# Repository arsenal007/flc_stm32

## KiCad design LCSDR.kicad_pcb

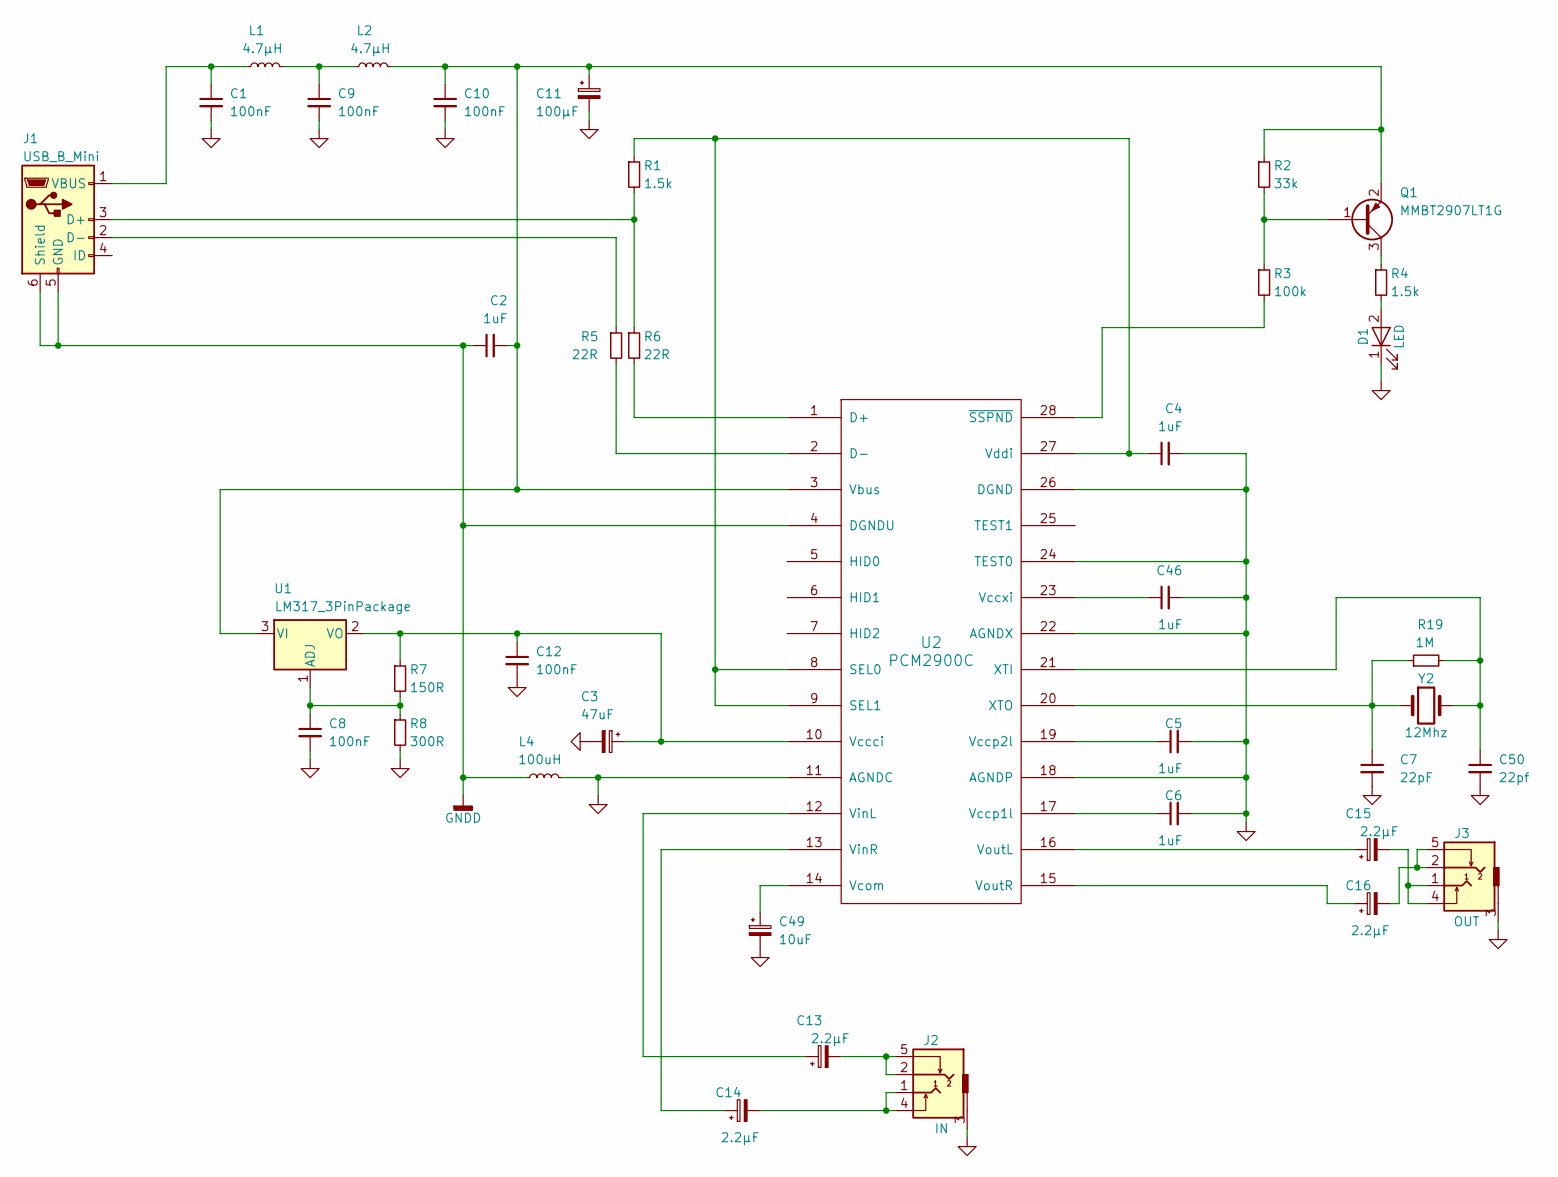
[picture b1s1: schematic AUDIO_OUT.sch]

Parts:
C1, C8, C9, C10, C12: 100nF; C_1206_0603
C2, C4, C5, C6, C46: 1uF; C_1206_0603
C3: 47uF; CP_Tantalum_Case-D_EIA-7343-31_Wave
C7: 22pF; C_1206_0603
C11: 100µF; CP_Tantalum_Case-D_EIA-7343-31_Wave
C13, C14, C15, C16: 2.2µF; CP_Tantalum_Case-A_EIA-3216-18_Wave
C49: 10uF; CP_Tantalum_Case-A_EIA-3216-18_Wave
C50: 22pf; C_1206_0603
D1: LED; LED_0603_HandSoldering
J1: USB_B_Mini; USB_Mini-B
J2: IN; audio_jack_3_5mm_PJ307
J3: OUT; audio_jack_3_5mm_PJ307
L1, L2: 4.7µH; Choke_CD54
L4: 100uH; Choke_Horizontal_RM10mm
Q1: MMBT2907LT1G; SOT-23
R1, R4: 1.5k; R_1206_0603
R2: 33k; R_1206_0603
R3: 100k; R_1206_0603
R5, R6: 22R; R_1206_0603
R7: 150R; R_1206_0603
R8: 300R; R_1206_0603
R19: 1M; R_1206_0603
U1: LM317_3PinPackage; SOT-223-3_TabPin2
U2: PCM2900C; SSOP-28_5.3x10.2mm_Pitch0.65mm
Y2: 12Mhz; Crystal_HC49-U_Vertical

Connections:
GND: C1.2, C3.2, C4.2, C5.2, C6.2, C7.2, C8.2, C9.2, C10.2, C11.2, C12.2, C46.2, C49.2, C50.2, D1.1 (K), J2.3, J3.3, L4.2, R8.2, U2.11 (AGNDC), U2.18 (AGNDP), U2.22 (AGNDX), U2.24 (TEST0), U2.26 (DGND)
GNDD: C2.1, J1.5 (GND), J1.6 (Shield), L4.1, U2.4 (DGNDU)
unnamed: C1.1, J1.1 (VBUS), L1.1
unnamed: C4.1, R1.1, U2.8 (SEL0), U2.9 (SEL1), U2.27 (Vddi)
unnamed: C5.1, U2.19 (Vccp2l)
unnamed: C6.1, U2.17 (Vccp1l)
unnamed: C7.1, R19.1, U2.20 (XTO), Y2.1
unnamed: C8.1, R7.2, R8.1, U1.1 (ADJ)
unnamed: C9.1, L1.2, L2.1
unnamed: C2.2, C10.1, C11.1, L2.2, Q1.2 (E), R2.1, U1.3 (VI), U2.3 (Vbus)
unnamed: C3.1, C12.1, R7.1, U1.2 (VO), U2.10 (Vccci)
unnamed: C13.1, U2.12 (VinL)
unnamed: C13.2, J2.2, J2.5
unnamed: C14.1, U2.13 (VinR)
unnamed: C14.2, J2.1, J2.4
unnamed: C15.1, U2.16 (VoutL)
unnamed: C15.2, J3.1, J3.4
unnamed: C16.1, U2.15 (VoutR)
unnamed: C16.2, J3.2, J3.5
unnamed: C46.1, U2.23 (Vccxi)
unnamed: C49.1, U2.14 (Vcom)
unnamed: C50.1, R19.2, U2.21 (XTI), Y2.2
unnamed: D1.2 (A), R4.2
unnamed: J1.2 (D-), R5.1
unnamed: J1.3 (D+), R1.2, R6.1
unnamed: Q1.1 (B), R2.2, R3.1
unnamed: Q1.3 (C), R4.1
unnamed: R3.2, U2.28 (~SSPND)
unnamed: R5.2, U2.2 (D-)
unnamed: R6.2, U2.1 (D+)

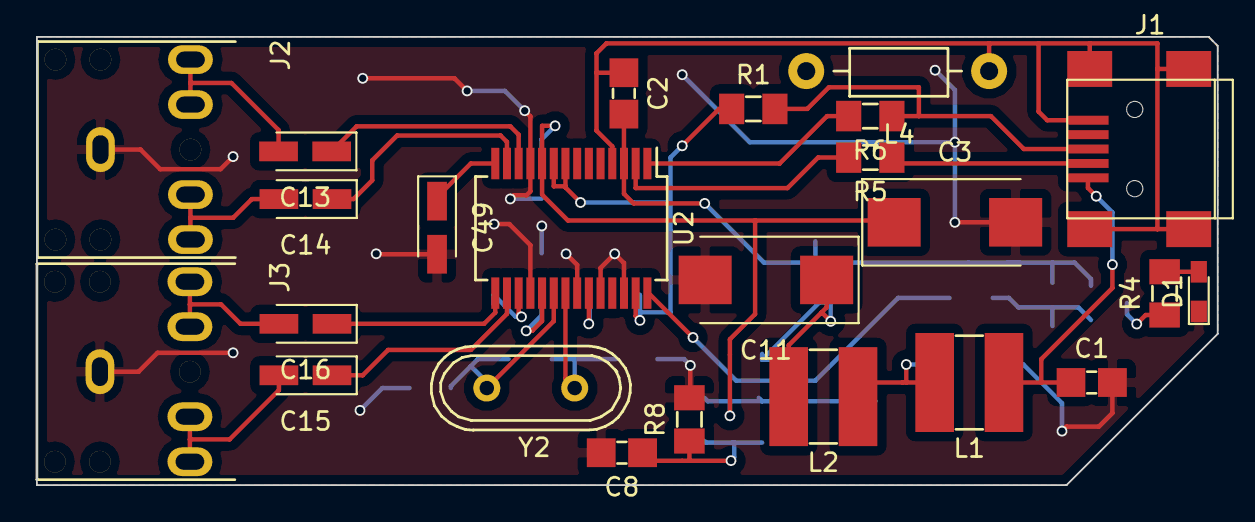
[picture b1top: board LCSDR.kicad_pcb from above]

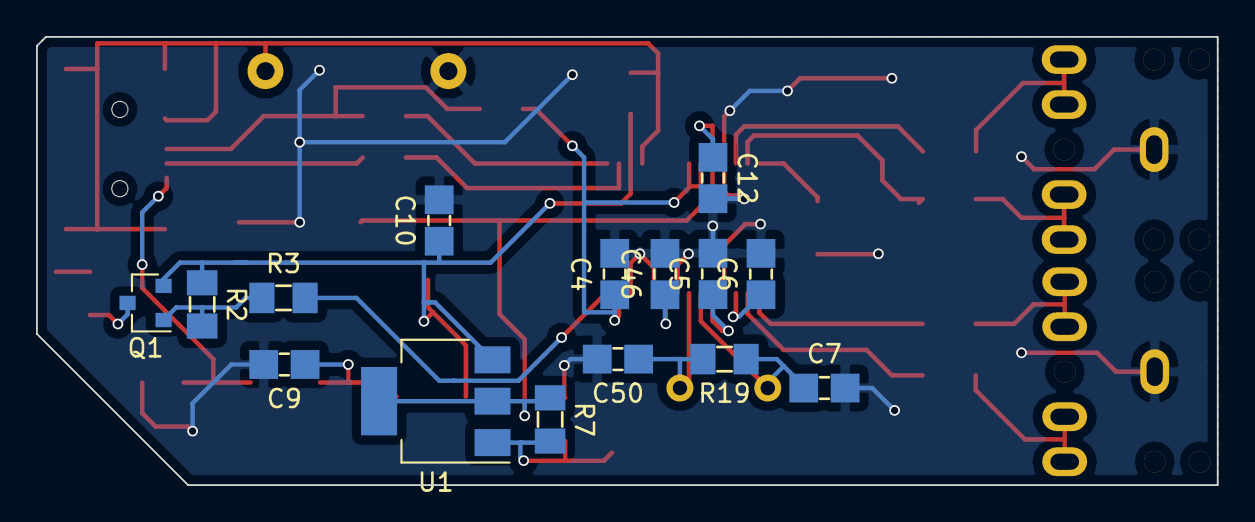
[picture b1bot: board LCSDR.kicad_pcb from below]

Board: 2 copper layers, 65.6 x 24.9 mm, 39 parts (15 on the bottom side), 30 nets.
